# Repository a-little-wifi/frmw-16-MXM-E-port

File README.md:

# MXM GPU + Dell E-Port expansion card for 16" Framework laptop

This is a board meant to fit in the GPU expansion bay of the 16" Framework laptop. Its primary purpose is to add Dell E-port dock support, but since that requires display outputs, an MXM GPU slot is added as well.

This is a very unfinished project that I started when the 16" Framework laptop was announced, but I probably won't be working on it much anymore since I don't plan on actually buying the laptop. I'm putting it here for anyone who might be interested.

The intent was to use the RP2040 to deal with dock port interfaces such as PS/2, I2S audio, and whatever other control signals it needs to function.

MXM part is based on my work on another project: MXM Immobilizer, a PCIe to MXM adapter.

I've manually created the E-port dock connector footprint from the part datasheet: https://www.mouser.com/pdfdocs/JAEMB-0200-1E_WD2.pdf

Dell's E-port dock uses the JAE WD2 series dock connectors. Part numbers commonly mentioned in applicable schematics are:
* JAE_WD2F144WB5R400 (M4800)
* JAE_WD2F144WB1R300 (E6440)
* JAE_WD2F144WBHR500-DT (E7470)
* JAE_WD2F144WD3 (E4300)
* JAE_WD2F144WD4 (E4200)
* JAE_WD2F144WB3R300 (E4310)
* JAE_WD2F144WB7-DT (E7440)
* JAE_WD2F144WB1 (E6400)

Plus a Foxconn alternative used in some of the last models:
* FOX_QL01723-D265G1-8H (Precision 7510)

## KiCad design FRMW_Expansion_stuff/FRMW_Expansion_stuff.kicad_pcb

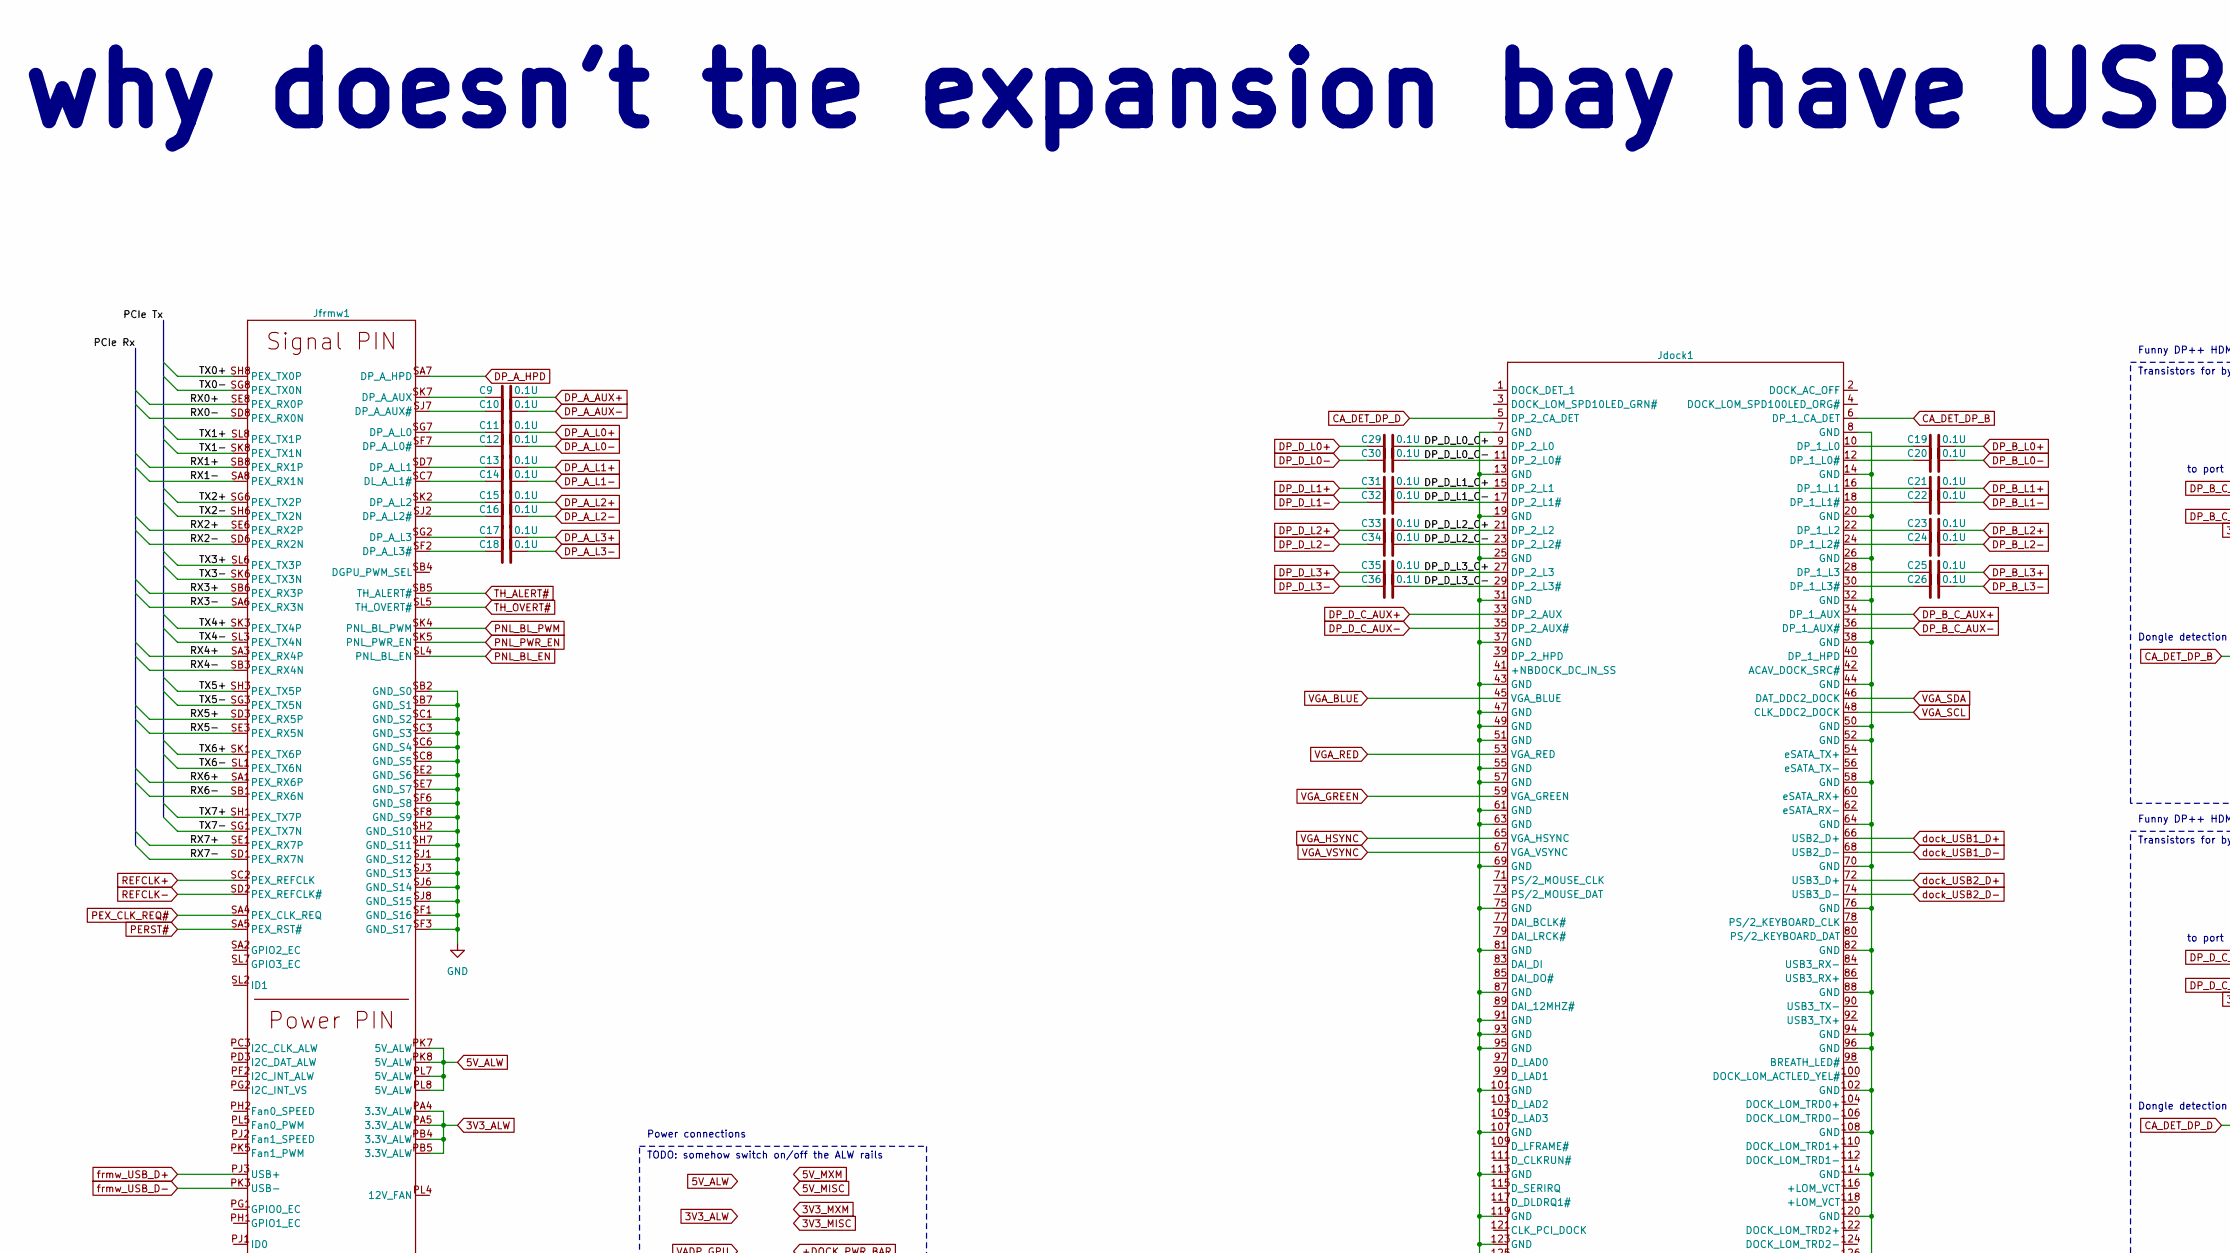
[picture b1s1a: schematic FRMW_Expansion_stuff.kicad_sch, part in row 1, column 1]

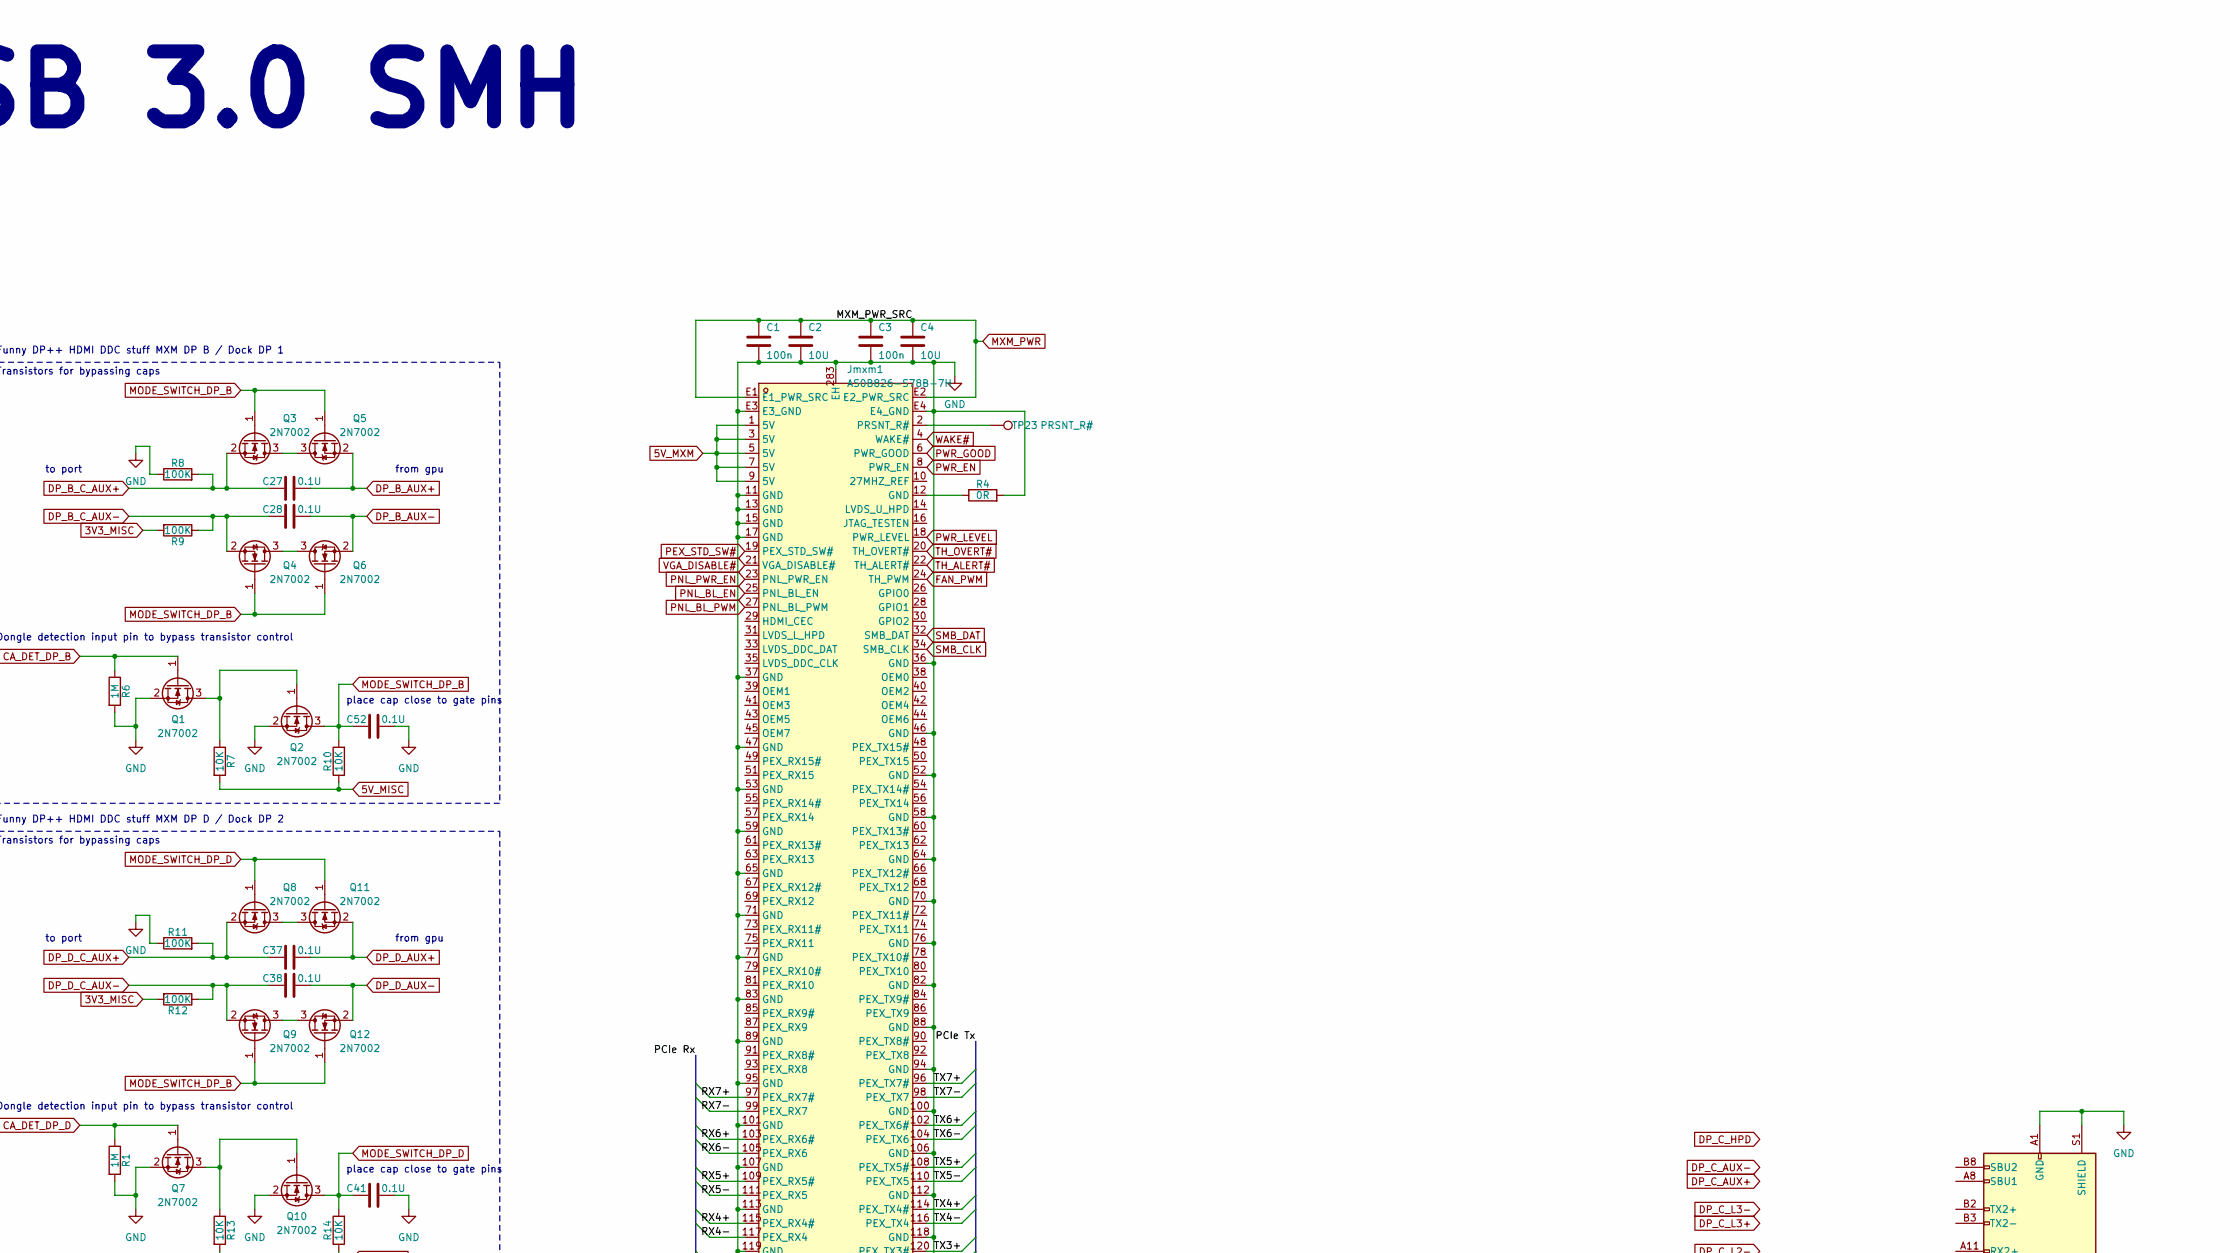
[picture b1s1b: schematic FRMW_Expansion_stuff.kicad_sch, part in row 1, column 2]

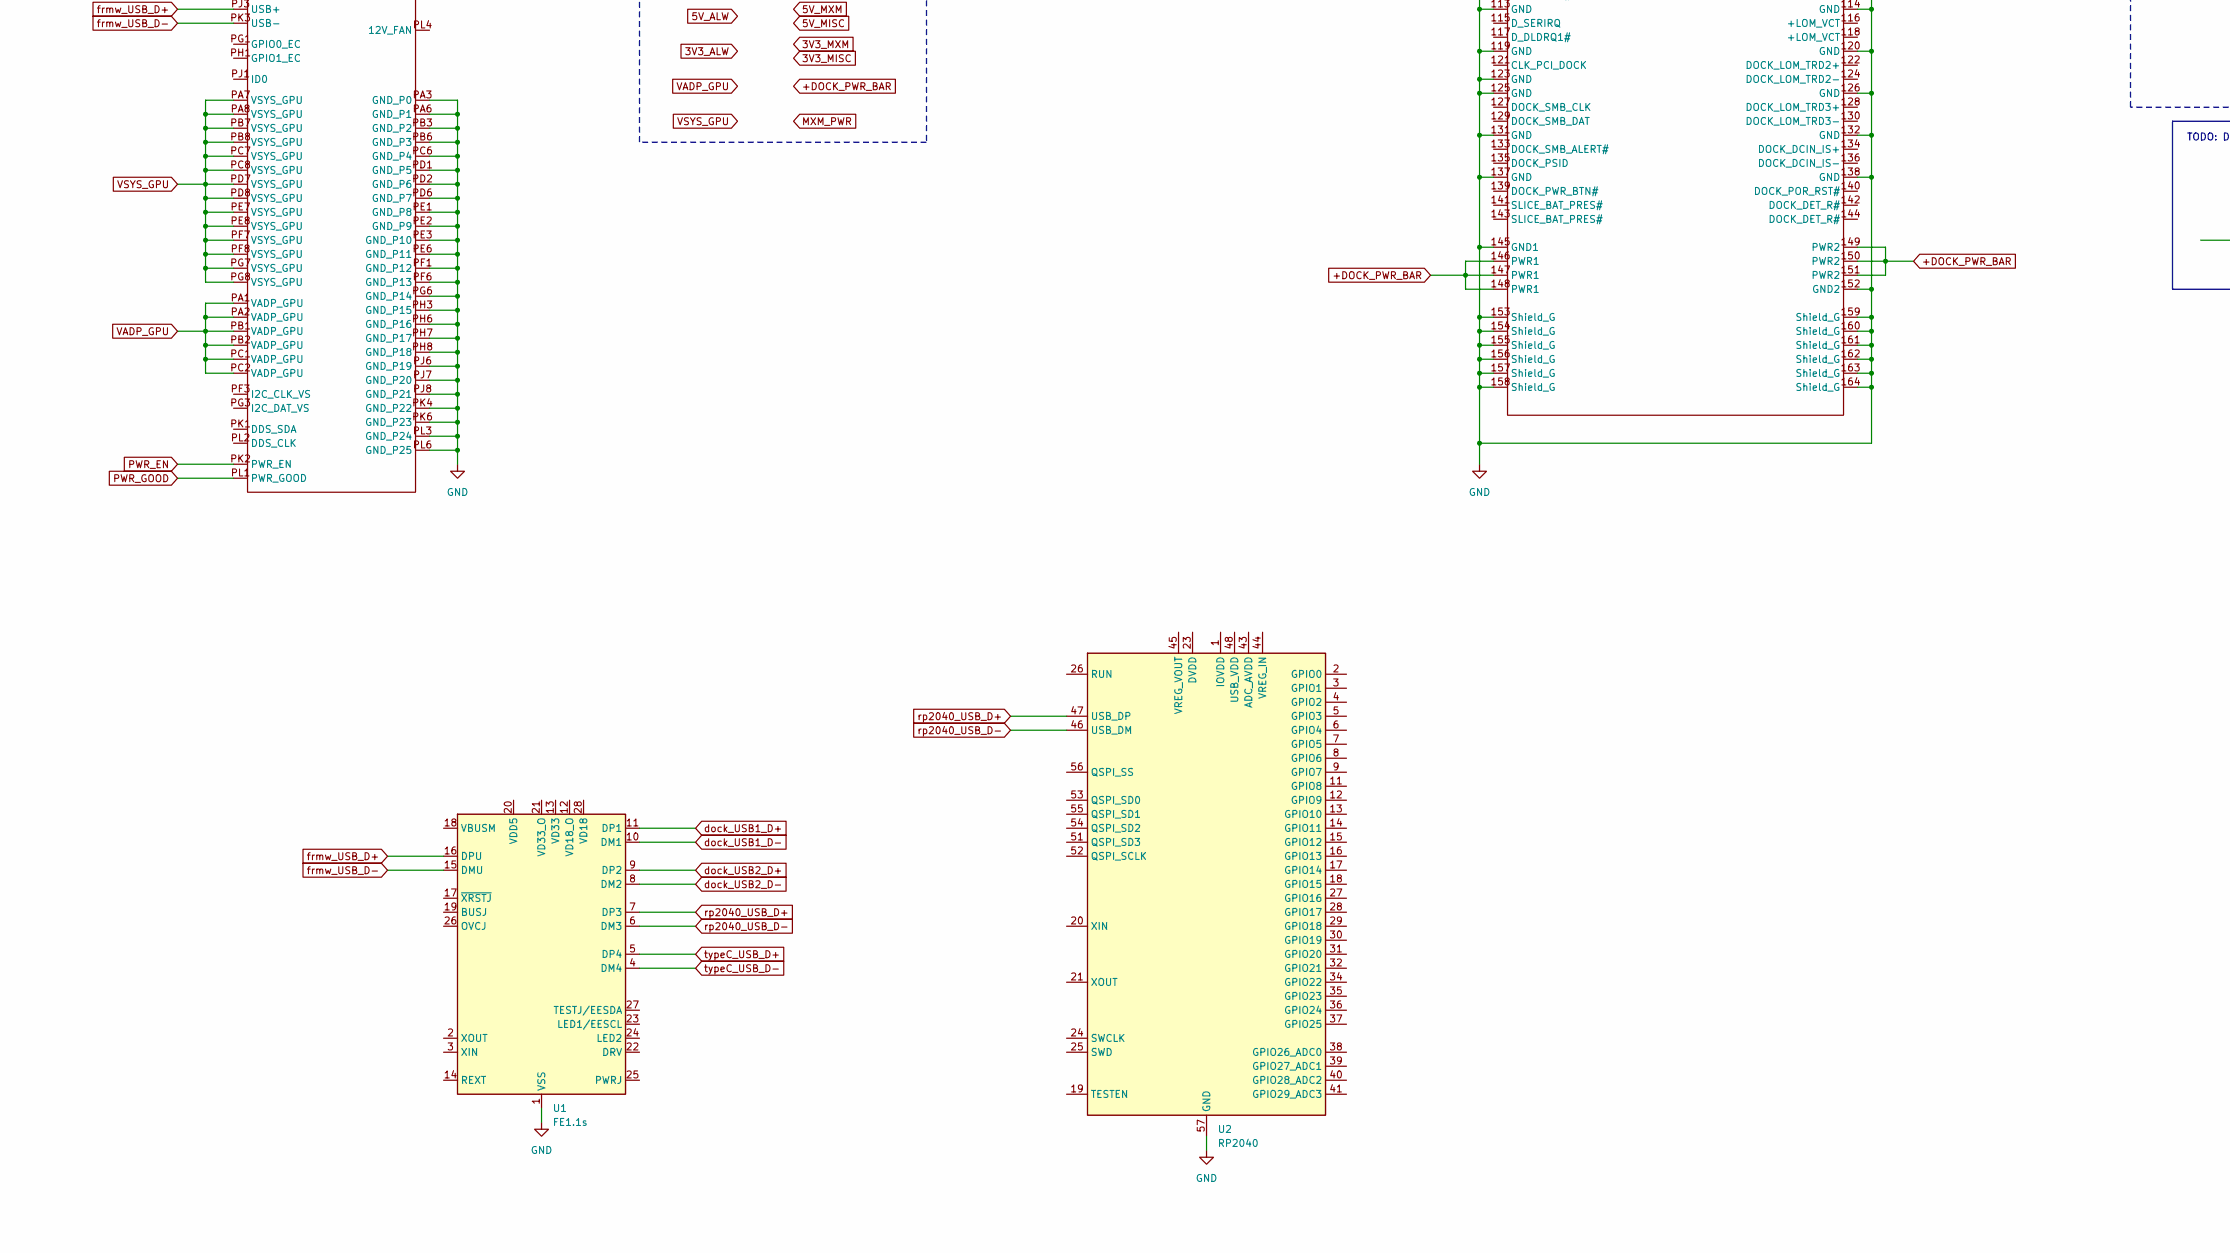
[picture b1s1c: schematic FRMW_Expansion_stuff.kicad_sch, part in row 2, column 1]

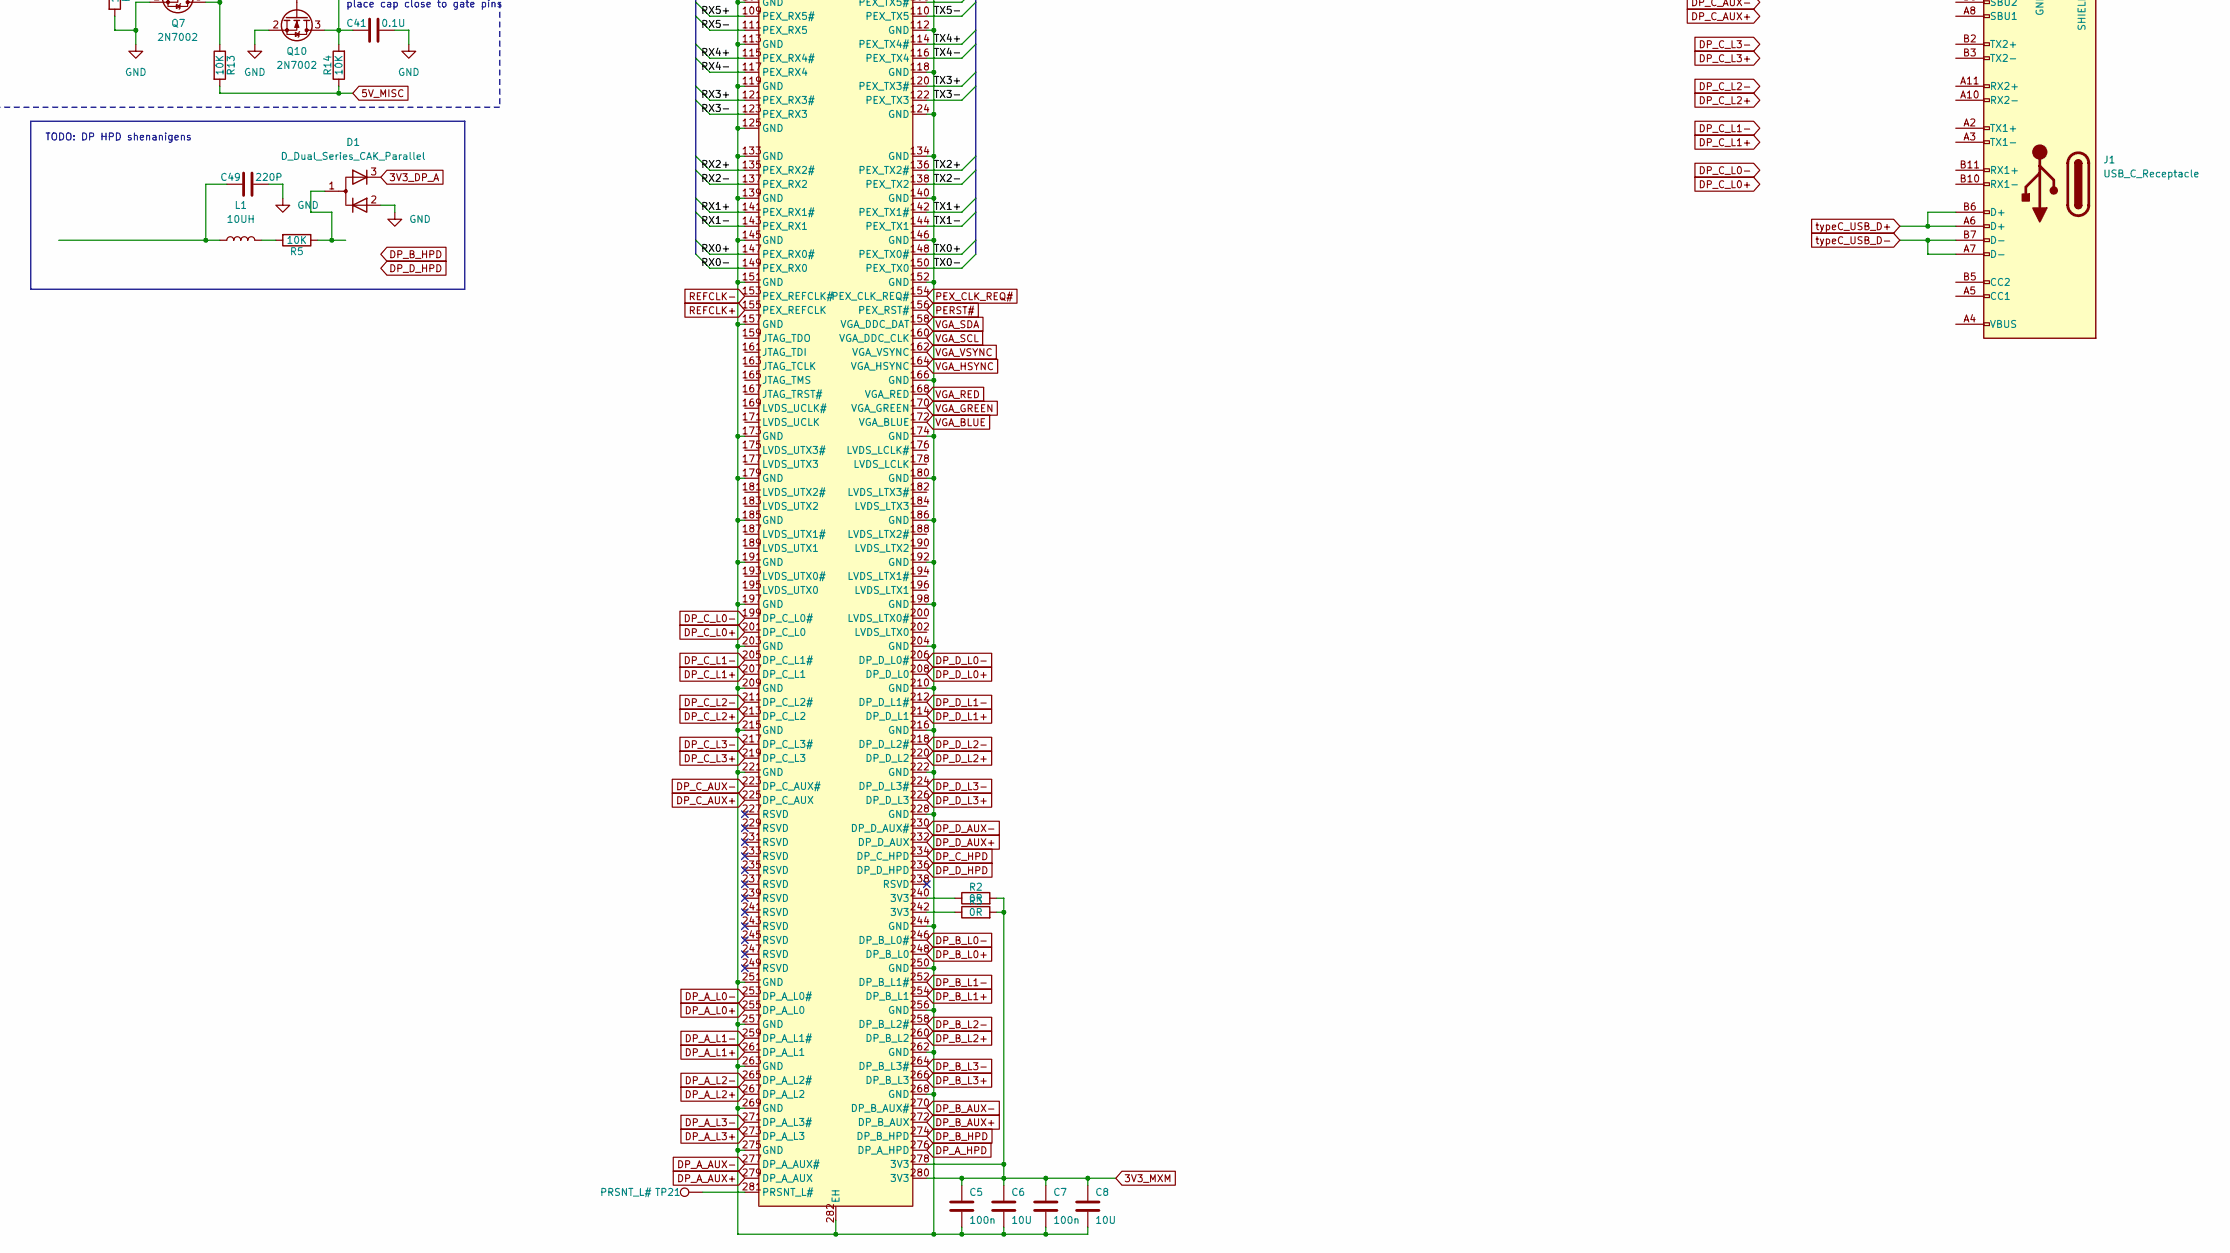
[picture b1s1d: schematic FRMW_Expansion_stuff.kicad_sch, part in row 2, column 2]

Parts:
C1, C3, C5, C7: 100n; C_0603_1608Metric
C2, C4, C6, C8: 10U; C_0603_1608Metric_Pad1.08x0.95mm_HandSolder
C9, C10, C11, C12, C13, C14, C15, C16, C17, C18, C19, C20, C21, C22, C23, C24, C25, C26, C27, C28, C29, C30, C31, C32, C33, C34, C35, C36, C37, C38: 0.1U; C_0402_1005Metric
C41, C52: 0.1U; C_0603_1608Metric
C49: 220P; C_0603_1608Metric
D1: D_Dual_Series_CAK_Parallel; SOT-23
J1: USB_C_Receptacle; USB_C_Receptacle_Amphenol_12401548E4-2A
Jdock1: DellDock
Jfrmw1: Expansion_Bay_FXBeam
Jmxm1: AS0B826-S78B-7H; CONN-SMD_AS0B826-S78B-7H; LCSC Part C426232
L1: 10UH; L_0603_1608Metric_Pad1.05x0.95mm_HandSolder
Q1, Q2, Q3, Q4, Q5, Q6, Q7, Q8, Q9, Q10, Q11, Q12: 2N7002; SOT-23
R1, R6: 1M; R_0603_1608Metric
R2, R3, R4: 0R; R_0603_1608Metric
R5, R7, R10, R13, R14: 10K; R_0603_1608Metric
R8, R9, R11, R12: 100K; R_0603_1608Metric
TP21: PRSNT_L#; TestPoint_Pad_D1.5mm
TP23: PRSNT_R#; TestPoint_Pad_D1.5mm
U1: FE1.1s; SSOP-28_3.9x9.9mm_P0.635mm
U2: RP2040; QFN-56-1EP_7x7mm_P0.4mm_EP3.2x3.2mm

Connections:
3V3_ALW: Jfrmw1.PA4 (3.3V_ALW), Jfrmw1.PA5 (3.3V_ALW), Jfrmw1.PB4 (3.3V_ALW), Jfrmw1.PB5 (3.3V_ALW)
3V3_DP_A: D1.3 (K)
3V3_MISC: R9.2, R12.2
3V3_MXM: C5.1, C6.1, C7.1, C8.1, Jmxm1.278 (3V3), Jmxm1.280 (3V3), R2.2, R3.2
5V_ALW: Jfrmw1.PK7 (5V_ALW), Jfrmw1.PK8 (5V_ALW), Jfrmw1.PL7 (5V_ALW), Jfrmw1.PL8 (5V_ALW)
5V_MISC: R7.2, R10.1, R13.2, R14.1
5V_MXM: Jmxm1.1 (5V), Jmxm1.3 (5V), Jmxm1.5 (5V), Jmxm1.7 (5V), Jmxm1.9 (5V)
+DOCK_PWR_BAR: Jdock1.146 (PWR1), Jdock1.147 (PWR1), Jdock1.148 (PWR1), Jdock1.149 (PWR2), Jdock1.150 (PWR2), Jdock1.151 (PWR2)
/DP_D_L0_C+: C29.1, Jdock1.9 (DP_2_L0)
/DP_D_L0_C-: C30.1, Jdock1.11 (DP_2_L0#)
/DP_D_L1_C+: C31.1, Jdock1.15 (DP_2_L1)
/DP_D_L1_C-: C32.1, Jdock1.17 (DP_2_L1#)
/DP_D_L2_C+: C33.1, Jdock1.21 (DP_2_L2)
/DP_D_L2_C-: C34.1, Jdock1.23 (DP_2_L2#)
/DP_D_L3_C+: C35.1, Jdock1.27 (DP_2_L3)
/DP_D_L3_C-: C36.1, Jdock1.29 (DP_2_L3#)
/RX0+: Jfrmw1.SE8 (PEX_RX0P), Jmxm1.147 (PEX_RX0#)
/RX0-: Jfrmw1.SD8 (PEX_RX0N), Jmxm1.149 (PEX_RX0)
/RX1+: Jfrmw1.SB8 (PEX_RX1P), Jmxm1.141 (PEX_RX1#)
/RX1-: Jfrmw1.SA8 (PEX_RX1N), Jmxm1.143 (PEX_RX1)
/RX2+: Jfrmw1.SE6 (PEX_RX2P), Jmxm1.135 (PEX_RX2#)
/RX2-: Jfrmw1.SD6 (PEX_RX2N), Jmxm1.137 (PEX_RX2)
/RX3+: Jfrmw1.SB6 (PEX_RX3P), Jmxm1.121 (PEX_RX3#)
/RX3-: Jfrmw1.SA6 (PEX_RX3N), Jmxm1.123 (PEX_RX3)
/RX4+: Jfrmw1.SA3 (PEX_RX4P), Jmxm1.115 (PEX_RX4#)
/RX4-: Jfrmw1.SB3 (PEX_RX4N), Jmxm1.117 (PEX_RX4)
/RX5+: Jfrmw1.SD3 (PEX_RX5P), Jmxm1.109 (PEX_RX5#)
/RX5-: Jfrmw1.SE3 (PEX_RX5N), Jmxm1.111 (PEX_RX5)
/RX6+: Jfrmw1.SA1 (PEX_RX6P), Jmxm1.103 (PEX_RX6#)
/RX6-: Jfrmw1.SB1 (PEX_RX6N), Jmxm1.105 (PEX_RX6)
/RX7+: Jfrmw1.SE1 (PEX_RX7P), Jmxm1.97 (PEX_RX7#)
/RX7-: Jfrmw1.SD1 (PEX_RX7N), Jmxm1.99 (PEX_RX7)
/TX0+: Jfrmw1.SH8 (PEX_TX0P), Jmxm1.148 (PEX_TX0#)
/TX0-: Jfrmw1.SG8 (PEX_TX0N), Jmxm1.150 (PEX_TX0)
/TX1+: Jfrmw1.SL8 (PEX_TX1P), Jmxm1.142 (PEX_TX1#)
/TX1-: Jfrmw1.SK8 (PEX_TX1N), Jmxm1.144 (PEX_TX1)
/TX2+: Jfrmw1.SG6 (PEX_TX2P), Jmxm1.136 (PEX_TX2#)
/TX2-: Jfrmw1.SH6 (PEX_TX2N), Jmxm1.138 (PEX_TX2)
/TX3+: Jfrmw1.SL6 (PEX_TX3P), Jmxm1.120 (PEX_TX3#)
/TX3-: Jfrmw1.SK6 (PEX_TX3N), Jmxm1.122 (PEX_TX3)
/TX4+: Jfrmw1.SK3 (PEX_TX4P), Jmxm1.114 (PEX_TX4#)
/TX4-: Jfrmw1.SL3 (PEX_TX4N), Jmxm1.116 (PEX_TX4)
/TX5+: Jfrmw1.SH3 (PEX_TX5P), Jmxm1.108 (PEX_TX5#)
/TX5-: Jfrmw1.SG3 (PEX_TX5N), Jmxm1.110 (PEX_TX5)
/TX6+: Jfrmw1.SK1 (PEX_TX6P), Jmxm1.102 (PEX_TX6#)
/TX6-: Jfrmw1.SL1 (PEX_TX6N), Jmxm1.104 (PEX_TX6)
/TX7+: Jfrmw1.SH1 (PEX_TX7P), Jmxm1.96 (PEX_TX7#)
/TX7-: Jfrmw1.SG1 (PEX_TX7N), Jmxm1.98 (PEX_TX7)
CA_DET_DP_B: Jdock1.6 (DP_1_CA_DET), Q1.1 (G), R6.1
CA_DET_DP_D: Jdock1.5 (DP_2_CA_DET), Q7.1 (G), R1.1
DP_A_AUX+: C9.1, Jmxm1.279 (DP_A_AUX)
DP_A_AUX-: C10.1, Jmxm1.277 (DP_A_AUX#)
DP_A_HPD: Jfrmw1.SA7 (DP_A_HPD), Jmxm1.276 (DP_A_HPD)
DP_A_L0+: C11.1, Jmxm1.255 (DP_A_L0)
DP_A_L0-: C12.1, Jmxm1.253 (DP_A_L0#)
DP_A_L1+: C13.1, Jmxm1.261 (DP_A_L1)
DP_A_L1-: C14.1, Jmxm1.259 (DP_A_L1#)
DP_A_L2+: C15.1, Jmxm1.267 (DP_A_L2)
DP_A_L2-: C16.1, Jmxm1.265 (DP_A_L2#)
DP_A_L3+: C17.1, Jmxm1.273 (DP_A_L3)
DP_A_L3-: C18.1, Jmxm1.271 (DP_A_L3#)
DP_B_AUX+: C27.1, Jmxm1.272 (DP_B_AUX), Q5.2 (S)
DP_B_AUX-: C28.1, Jmxm1.270 (DP_B_AUX#), Q6.2 (S)
DP_B_C_AUX+: C27.2, Jdock1.34 (DP_1_AUX), Q3.2 (S), R8.2
DP_B_C_AUX-: C28.2, Jdock1.36 (DP_1_AUX#), Q4.2 (S), R9.1
DP_B_HPD: Jmxm1.274 (DP_B_HPD)
DP_B_L0+: C19.1, Jmxm1.248 (DP_B_L0)
DP_B_L0-: C20.1, Jmxm1.246 (DP_B_L0#)
DP_B_L1+: C21.1, Jmxm1.254 (DP_B_L1)
DP_B_L1-: C22.1, Jmxm1.252 (DP_B_L1#)
DP_B_L2+: C23.1, Jmxm1.260 (DP_B_L2)
DP_B_L2-: C24.1, Jmxm1.258 (DP_B_L2#)
DP_B_L3+: C25.1, Jmxm1.266 (DP_B_L3)
DP_B_L3-: C26.1, Jmxm1.264 (DP_B_L3#)
DP_C_AUX+: Jmxm1.225 (DP_C_AUX)
DP_C_AUX-: Jmxm1.223 (DP_C_AUX#)
DP_C_HPD: Jmxm1.234 (DP_C_HPD)
DP_C_L0+: Jmxm1.201 (DP_C_L0)
DP_C_L0-: Jmxm1.199 (DP_C_L0#)
DP_C_L1+: Jmxm1.207 (DP_C_L1)
DP_C_L1-: Jmxm1.205 (DP_C_L1#)
DP_C_L2+: Jmxm1.213 (DP_C_L2)
DP_C_L2-: Jmxm1.211 (DP_C_L2#)
DP_C_L3+: Jmxm1.219 (DP_C_L3)
DP_C_L3-: Jmxm1.217 (DP_C_L3#)
DP_D_AUX+: C37.1, Jmxm1.232 (DP_D_AUX), Q11.2 (S)
DP_D_AUX-: C38.1, Jmxm1.230 (DP_D_AUX#), Q12.2 (S)
DP_D_C_AUX+: C37.2, Jdock1.33 (DP_2_AUX), Q8.2 (S), R11.2
DP_D_C_AUX-: C38.2, Jdock1.35 (DP_2_AUX#), Q9.2 (S), R12.1
DP_D_HPD: Jmxm1.236 (DP_D_HPD)
DP_D_L0+: C29.2, Jmxm1.208 (DP_D_L0)
DP_D_L0-: C30.2, Jmxm1.206 (DP_D_L0#)
DP_D_L1+: C31.2, Jmxm1.214 (DP_D_L1)
DP_D_L1-: C32.2, Jmxm1.212 (DP_D_L1#)
DP_D_L2+: C33.2, Jmxm1.220 (DP_D_L2)
DP_D_L2-: C34.2, Jmxm1.218 (DP_D_L2#)
DP_D_L3+: C35.2, Jmxm1.226 (DP_D_L3)
DP_D_L3-: C36.2, Jmxm1.224 (DP_D_L3#)
FAN_PWM: Jmxm1.24 (TH_PWM)
GND: C1.2, C2.2, C3.2, C4.2, C5.2, C6.2, C7.2, C8.2, C41.1, C49.1, C52.1, D1.2 (K), J1.A1 (GND), J1.A12 (GND), J1.B1 (GND), J1.B12 (GND), J1.S1 (SHIELD), Jdock1.7 (GND), Jdock1.8 (GND), Jdock1.13 (GND), Jdock1.14 (GND), Jdock1.19 (GND), Jdock1.20 (GND), Jdock1.25 (GND), Jdock1.26 (GND), Jdock1.31 (GND), Jdock1.32 (GND), Jdock1.37 (GND), Jdock1.38 (GND), Jdock1.43 (GND), Jdock1.44 (GND), Jdock1.47 (GND), Jdock1.49 (GND), Jdock1.50 (GND), Jdock1.51 (GND), Jdock1.52 (GND), Jdock1.55 (GND), Jdock1.57 (GND), Jdock1.58 (GND), Jdock1.61 (GND), Jdock1.63 (GND), Jdock1.64 (GND), Jdock1.69 (GND), Jdock1.70 (GND), Jdock1.75 (GND), Jdock1.76 (GND), Jdock1.81 (GND), Jdock1.82 (GND), Jdock1.87 (GND), Jdock1.88 (GND), Jdock1.91 (GND), Jdock1.93 (GND), Jdock1.94 (GND), Jdock1.95 (GND), Jdock1.96 (GND), Jdock1.101 (GND), Jdock1.102 (GND), Jdock1.107 (GND), Jdock1.108 (GND), Jdock1.113 (GND), Jdock1.114 (GND), Jdock1.119 (GND), Jdock1.120 (GND), Jdock1.123 (GND), Jdock1.125 (GND), Jdock1.126 (GND), Jdock1.131 (GND), Jdock1.132 (GND), Jdock1.137 (GND), Jdock1.138 (GND), Jdock1.145 (GND1), Jdock1.152 (GND2), Jdock1.153 (Shield_G), Jdock1.154 (Shield_G), Jdock1.155 (Shield_G), Jdock1.156 (Shield_G), Jdock1.157 (Shield_G), Jdock1.158 (Shield_G), Jdock1.159 (Shield_G), Jdock1.160 (Shield_G), Jdock1.161 (Shield_G), Jdock1.162 (Shield_G), Jdock1.163 (Shield_G), Jdock1.164 (Shield_G), Jfrmw1.PA3 (GND_P0), Jfrmw1.PA6 (GND_P1), Jfrmw1.PB3 (GND_P2), Jfrmw1.PB6 (GND_P3), Jfrmw1.PC6 (GND_P4), Jfrmw1.PD1 (GND_P5), Jfrmw1.PD2 (GND_P6), Jfrmw1.PD6 (GND_P7), Jfrmw1.PE1 (GND_P8), Jfrmw1.PE2 (GND_P9), Jfrmw1.PE3 (GND_P10), Jfrmw1.PE6 (GND_P11), Jfrmw1.PF1 (GND_P12), Jfrmw1.PF6 (GND_P13), Jfrmw1.PG6 (GND_P14), Jfrmw1.PH3 (GND_P15), Jfrmw1.PH6 (GND_P16), Jfrmw1.PH7 (GND_P17), Jfrmw1.PH8 (GND_P18), Jfrmw1.PJ6 (GND_P19), Jfrmw1.PJ7 (GND_P20), Jfrmw1.PJ8 (GND_P21), Jfrmw1.PK4 (GND_P22), Jfrmw1.PK6 (GND_P23), Jfrmw1.PL3 (GND_P24), Jfrmw1.PL6 (GND_P25), Jfrmw1.SB2 (GND_S0), Jfrmw1.SB7 (GND_S1), Jfrmw1.SC1 (GND_S2), Jfrmw1.SC3 (GND_S3), Jfrmw1.SC6 (GND_S4), Jfrmw1.SC8 (GND_S5), Jfrmw1.SE2 (GND_S6), Jfrmw1.SE7 (GND_S7), Jfrmw1.SF1 (GND_S16), Jfrmw1.SF3 (GND_S17), Jfrmw1.SF6 (GND_S8), Jfrmw1.SF8 (GND_S9), Jfrmw1.SH2 (GND_S10), Jfrmw1.SH7 (GND_S11), Jfrmw1.SJ1 (GND_S12), Jfrmw1.SJ3 (GND_S13), Jfrmw1.SJ6 (GND_S14), Jfrmw1.SJ8 (GND_S15), Jmxm1.11 (GND), Jmxm1.13 (GND), Jmxm1.15 (GND), Jmxm1.17 (GND), Jmxm1.36 (GND), Jmxm1.37 (GND), Jmxm1.46 (GND), Jmxm1.47 (GND), Jmxm1.52 (GND), Jmxm1.53 (GND), Jmxm1.58 (GND), Jmxm1.59 (GND), Jmxm1.64 (GND), Jmxm1.65 (GND), Jmxm1.70 (GND), Jmxm1.71 (GND), Jmxm1.76 (GND), Jmxm1.77 (GND), Jmxm1.82 (GND), Jmxm1.83 (GND), Jmxm1.88 (GND), Jmxm1.89 (GND), Jmxm1.94 (GND), Jmxm1.95 (GND), Jmxm1.100 (GND), Jmxm1.101 (GND), Jmxm1.106 (GND), Jmxm1.107 (GND), Jmxm1.112 (GND), Jmxm1.113 (GND), Jmxm1.118 (GND), Jmxm1.119 (GND), Jmxm1.124 (GND), Jmxm1.125 (GND), Jmxm1.133 (GND), Jmxm1.134 (GND), Jmxm1.139 (GND), Jmxm1.140 (GND), Jmxm1.145 (GND), Jmxm1.146 (GND), Jmxm1.151 (GND), Jmxm1.152 (GND), Jmxm1.157 (GND), Jmxm1.166 (GND), Jmxm1.173 (GND), Jmxm1.174 (GND), Jmxm1.179 (GND), Jmxm1.180 (GND), Jmxm1.185 (GND), Jmxm1.186 (GND), Jmxm1.191 (GND), Jmxm1.192 (GND), Jmxm1.197 (GND), Jmxm1.198 (GND), Jmxm1.203 (GND), Jmxm1.204 (GND), Jmxm1.209 (GND), Jmxm1.210 (GND), Jmxm1.215 (GND), Jmxm1.216 (GND), Jmxm1.221 (GND), Jmxm1.222 (GND), Jmxm1.228 (GND), Jmxm1.244 (GND), Jmxm1.250 (GND), Jmxm1.251 (GND), Jmxm1.256 (GND), Jmxm1.257 (GND), Jmxm1.262 (GND), Jmxm1.263 (GND), Jmxm1.268 (GND), Jmxm1.269 (GND), Jmxm1.275 (GND), Jmxm1.282 (EH), Jmxm1.283 (EH), Jmxm1.E3 (E3_GND), Jmxm1.E4 (E4_GND), Q1.2 (S), Q2.2 (S), Q7.2 (S), Q10.2 (S), R1.2, R4.2, R6.2, R8.1, R11.1, U1.1 (VSS), U2.57 (GND)
MODE_SWITCH_DP_B: C52.2, Q2.3 (D), Q3.1 (G), Q4.1 (G), Q5.1 (G), Q6.1 (G), Q9.1 (G), Q12.1 (G), R10.2
MODE_SWITCH_DP_D: C41.2, Q8.1 (G), Q10.3 (D), Q11.1 (G), R14.2
MXM_PWR: C1.1, C2.1, C3.1, C4.1, Jmxm1.E1 (E1_PWR_SRC), Jmxm1.E2 (E2_PWR_SRC)
unnamed: C49.2, L1.1
unnamed: D1.1 (A), R5.1
unnamed: J1.A4 (VBUS), J1.A9 (VBUS), J1.B4 (VBUS), J1.B9 (VBUS)
unnamed: C20.2, Jdock1.12 (DP_1_L0#)
unnamed: C19.2, Jdock1.10 (DP_1_L0)
unnamed: C22.2, Jdock1.18 (DP_1_L1#)
unnamed: C21.2, Jdock1.16 (DP_1_L1)
unnamed: C24.2, Jdock1.24 (DP_1_L2#)
unnamed: C23.2, Jdock1.22 (DP_1_L2)
unnamed: C26.2, Jdock1.30 (DP_1_L3#)
unnamed: C25.2, Jdock1.28 (DP_1_L3)
unnamed: C14.2, Jfrmw1.SC7 (DL_A_L1#)
unnamed: C10.2, Jfrmw1.SJ7 (DP_A_AUX#)
unnamed: C9.2, Jfrmw1.SK7 (DP_A_AUX)
unnamed: C12.2, Jfrmw1.SF7 (DP_A_L0#)
unnamed: C11.2, Jfrmw1.SG7 (DP_A_L0)
unnamed: C13.2, Jfrmw1.SD7 (DP_A_L1)
unnamed: C16.2, Jfrmw1.SJ2 (DP_A_L2#)
unnamed: C15.2, Jfrmw1.SK2 (DP_A_L2)
unnamed: C18.2, Jfrmw1.SF2 (DP_A_L3#)
unnamed: C17.2, Jfrmw1.SG2 (DP_A_L3)
unnamed: Jmxm1.240 (3V3), R2.1
unnamed: Jmxm1.242 (3V3), R3.1
unnamed: Jmxm1.12 (GND), R4.1
unnamed: Jmxm1.281 (PRSNT_L#), TP21.1
unnamed: Jmxm1.2 (PRSNT_R#), TP23.1
unnamed: L1.2, R5.2
unnamed: Q1.3 (D), Q2.1 (G), R7.1
unnamed: Q3.3 (D), Q5.3 (D)
unnamed: Q4.3 (D), Q6.3 (D)
unnamed: Q7.3 (D), Q10.1 (G), R13.1
unnamed: Q8.3 (D), Q11.3 (D)
unnamed: Q9.3 (D), Q12.3 (D)
unnamed: U2.23 (DVDD), U2.50 (DVDD)
unnamed: U2.1 (IOVDD), U2.10 (IOVDD), U2.22 (IOVDD), U2.33 (IOVDD), U2.42 (IOVDD), U2.49 (IOVDD)
PERST#: Jfrmw1.SA5 (PEX_RST#), Jmxm1.156 (PEX_RST#)
PEX_CLK_REQ#: Jfrmw1.SA4 (PEX_CLK_REQ), Jmxm1.154 (PEX_CLK_REQ#)
PEX_STD_SW#: Jmxm1.19 (PEX_STD_SW#)
PNL_BL_EN: Jfrmw1.SL4 (PNL_BL_EN), Jmxm1.25 (PNL_BL_EN)
PNL_BL_PWM: Jfrmw1.SK4 (PNL_BL_PWM), Jmxm1.27 (PNL_BL_PWM)
PNL_PWR_EN: Jfrmw1.SK5 (PNL_PWR_EN), Jmxm1.23 (PNL_PWR_EN)
PWR_EN: Jfrmw1.PK2 (PWR_EN), Jmxm1.8 (PWR_EN)
PWR_GOOD: Jfrmw1.PL1 (PWR_GOOD), Jmxm1.6 (PWR_GOOD)
PWR_LEVEL: Jmxm1.18 (PWR_LEVEL)
REFCLK+: Jfrmw1.SC2 (PEX_REFCLK), Jmxm1.155 (PEX_REFCLK)
REFCLK-: Jfrmw1.SD2 (PEX_REFCLK#), Jmxm1.153 (PEX_REFCLK#)
SMB_CLK: Jmxm1.34 (SMB_CLK)
SMB_DAT: Jmxm1.32 (SMB_DAT)
TH_ALERT#: Jfrmw1.SB5 (TH_ALERT#), Jmxm1.22 (TH_ALERT#)
TH_OVERT#: Jfrmw1.SL5 (TH_OVERT#), Jmxm1.20 (TH_OVERT#)
VADP_GPU: Jfrmw1.PA1 (VADP_GPU), Jfrmw1.PA2 (VADP_GPU), Jfrmw1.PB1 (VADP_GPU), Jfrmw1.PB2 (VADP_GPU), Jfrmw1.PC1 (VADP_GPU), Jfrmw1.PC2 (VADP_GPU)
VGA_BLUE: Jdock1.45 (VGA_BLUE), Jmxm1.172 (VGA_BLUE)
VGA_DISABLE#: Jmxm1.21 (VGA_DISABLE#)
VGA_GREEN: Jdock1.59 (VGA_GREEN), Jmxm1.170 (VGA_GREEN)
VGA_HSYNC: Jdock1.65 (VGA_HSYNC), Jmxm1.164 (VGA_HSYNC)
VGA_RED: Jdock1.53 (VGA_RED), Jmxm1.168 (VGA_RED)
VGA_SCL: Jdock1.48 (CLK_DDC2_DOCK), Jmxm1.160 (VGA_DDC_CLK)
VGA_SDA: Jdock1.46 (DAT_DDC2_DOCK), Jmxm1.158 (VGA_DDC_DAT)
VGA_VSYNC: Jdock1.67 (VGA_VSYNC), Jmxm1.162 (VGA_VSYNC)
VSYS_GPU: Jfrmw1.PA7 (VSYS_GPU), Jfrmw1.PA8 (VSYS_GPU), Jfrmw1.PB7 (VSYS_GPU), Jfrmw1.PB8 (VSYS_GPU), Jfrmw1.PC7 (VSYS_GPU), Jfrmw1.PC8 (VSYS_GPU), Jfrmw1.PD7 (VSYS_GPU), Jfrmw1.PD8 (VSYS_GPU), Jfrmw1.PE7 (VSYS_GPU), Jfrmw1.PE8 (VSYS_GPU), Jfrmw1.PF7 (VSYS_GPU), Jfrmw1.PF8 (VSYS_GPU), Jfrmw1.PG7 (VSYS_GPU), Jfrmw1.PG8 (VSYS_GPU)
WAKE#: Jmxm1.4 (WAKE#)
dock_USB1_D+: Jdock1.66 (USB2_D+), U1.11 (DP1)
dock_USB1_D-: Jdock1.68 (USB2_D-), U1.10 (DM1)
dock_USB2_D+: Jdock1.72 (USB3_D+), U1.9 (DP2)
dock_USB2_D-: Jdock1.74 (USB3_D-), U1.8 (DM2)
frmw_USB_D+: Jfrmw1.PJ3 (USB+), U1.16 (DPU)
frmw_USB_D-: Jfrmw1.PK3 (USB-), U1.15 (DMU)
rp2040_USB_D+: U1.7 (DP3), U2.47 (USB_DP)
rp2040_USB_D-: U1.6 (DM3), U2.46 (USB_DM)
typeC_USB_D+: J1.A6 (D+), J1.B6 (D+), U1.5 (DP4)
typeC_USB_D-: J1.A7 (D-), J1.B7 (D-), U1.4 (DM4)

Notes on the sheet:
place cap close to gate pins
why doesn't the expansion bay have USB 3.0 SMH
Funny DP++ HDMI DDC stuff MXM DP B / Dock DP 1
Funny DP++ HDMI DDC stuff MXM DP D / Dock DP 2
Power connections
from gpu
to port
Transistors for bypassing caps
Dongle detection input pin to bypass transistor control
TODO: somehow switch on/off the ALW rails
TODO: DP HPD shenanigens

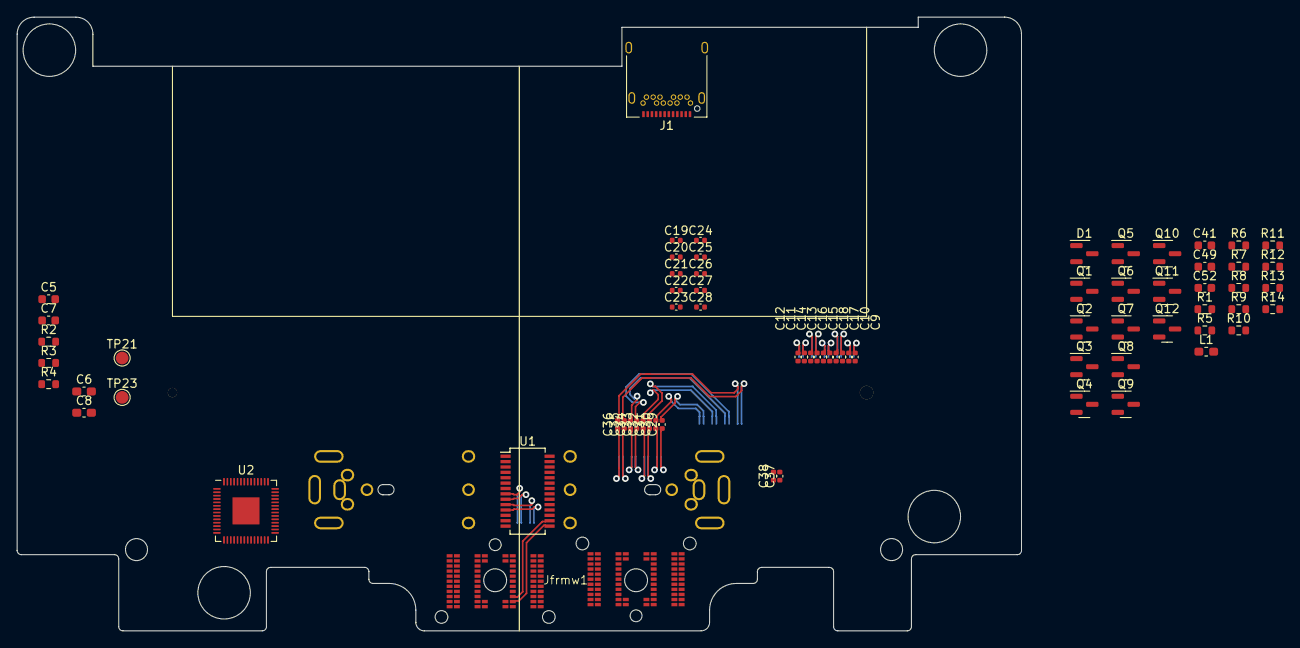
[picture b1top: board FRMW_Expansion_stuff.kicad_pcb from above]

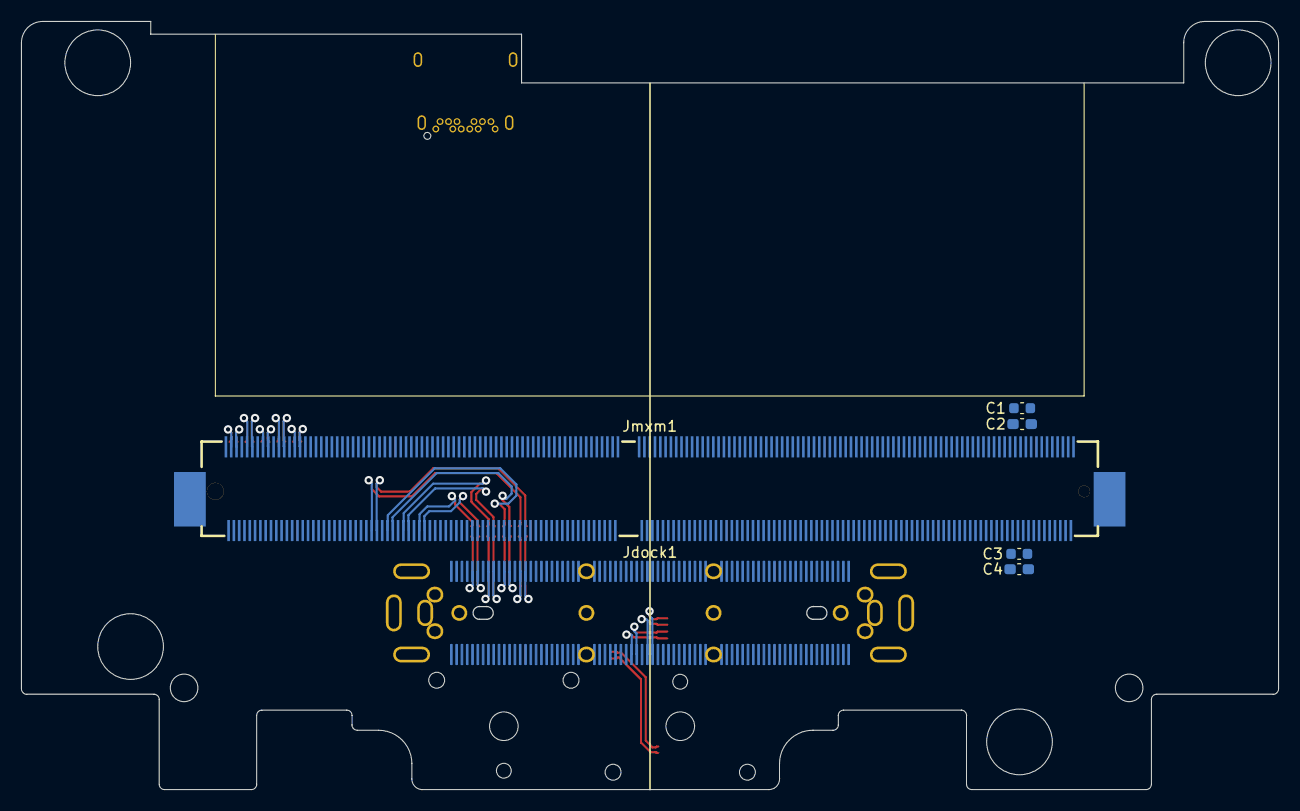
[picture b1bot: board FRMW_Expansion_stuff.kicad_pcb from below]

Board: 2 copper layers, 118.7 x 72.5 mm, 77 parts (6 on the bottom side), 153 nets.

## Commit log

2024-04-16 The files
2024-04-16 Wrote readme
2024-04-16 Added MXM Immobilizer mention
2024-04-16 Changed dock port datasheet link to the one I actually used
2024-04-16 Added E6400 dock port part and fixed typo
2025-03-22 added 3d model for dock port
    don't tell JAE I put the model online lol
2025-03-22 added the other 3d model lol
2025-03-23 the rest of the 3d models
